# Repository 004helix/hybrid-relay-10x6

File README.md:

# 10-channel hybrid relay din-rail module

- 4 units width
- 12/24v dc input
- reverse polarity protection
- mechanical relay sockets - `Finder 93.11`
- reinforced insulation using `VOT8024AG` optocouplers
- snubberless triacs as SSR - `BTA12-800BW / BTA16-800BW`
- 250VAC/6A slim mechanical relays - `Finder 34.51 / TE V23092 / Hongfa HF41F`
- MCU - `ATmega164PA-MU / ATmega324PA-MU / ATmega644PA-MU`
- triac test button
- open-drain input

[BOM](BOM.md)

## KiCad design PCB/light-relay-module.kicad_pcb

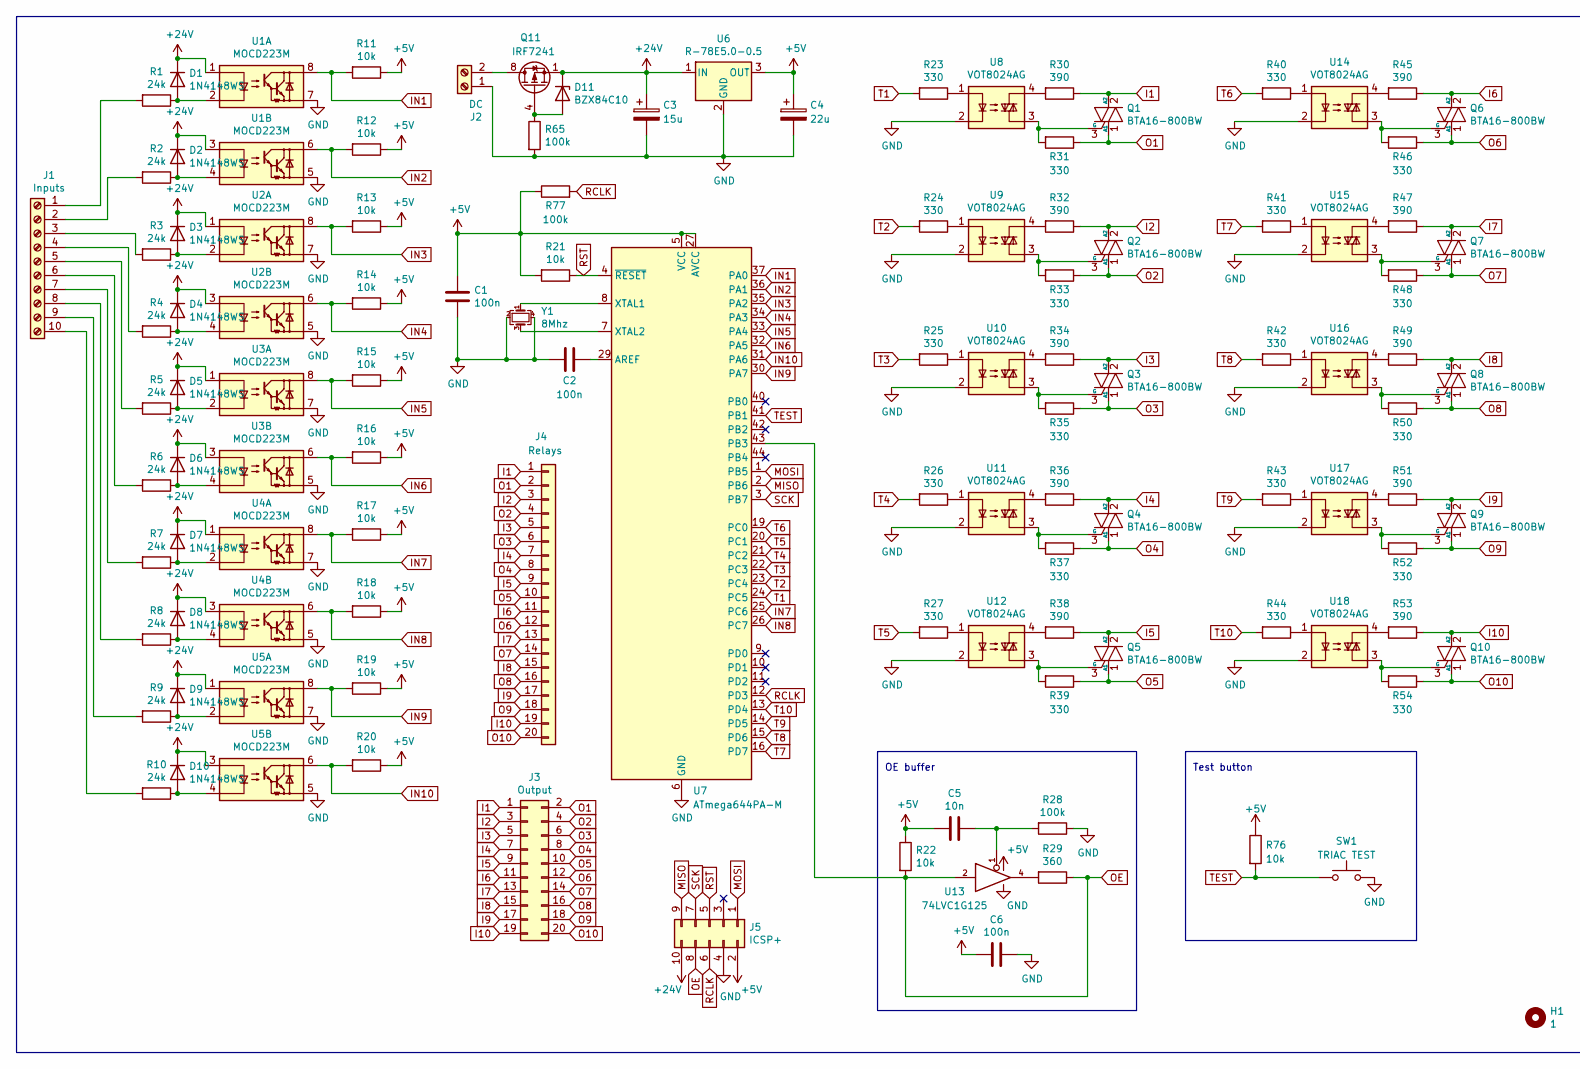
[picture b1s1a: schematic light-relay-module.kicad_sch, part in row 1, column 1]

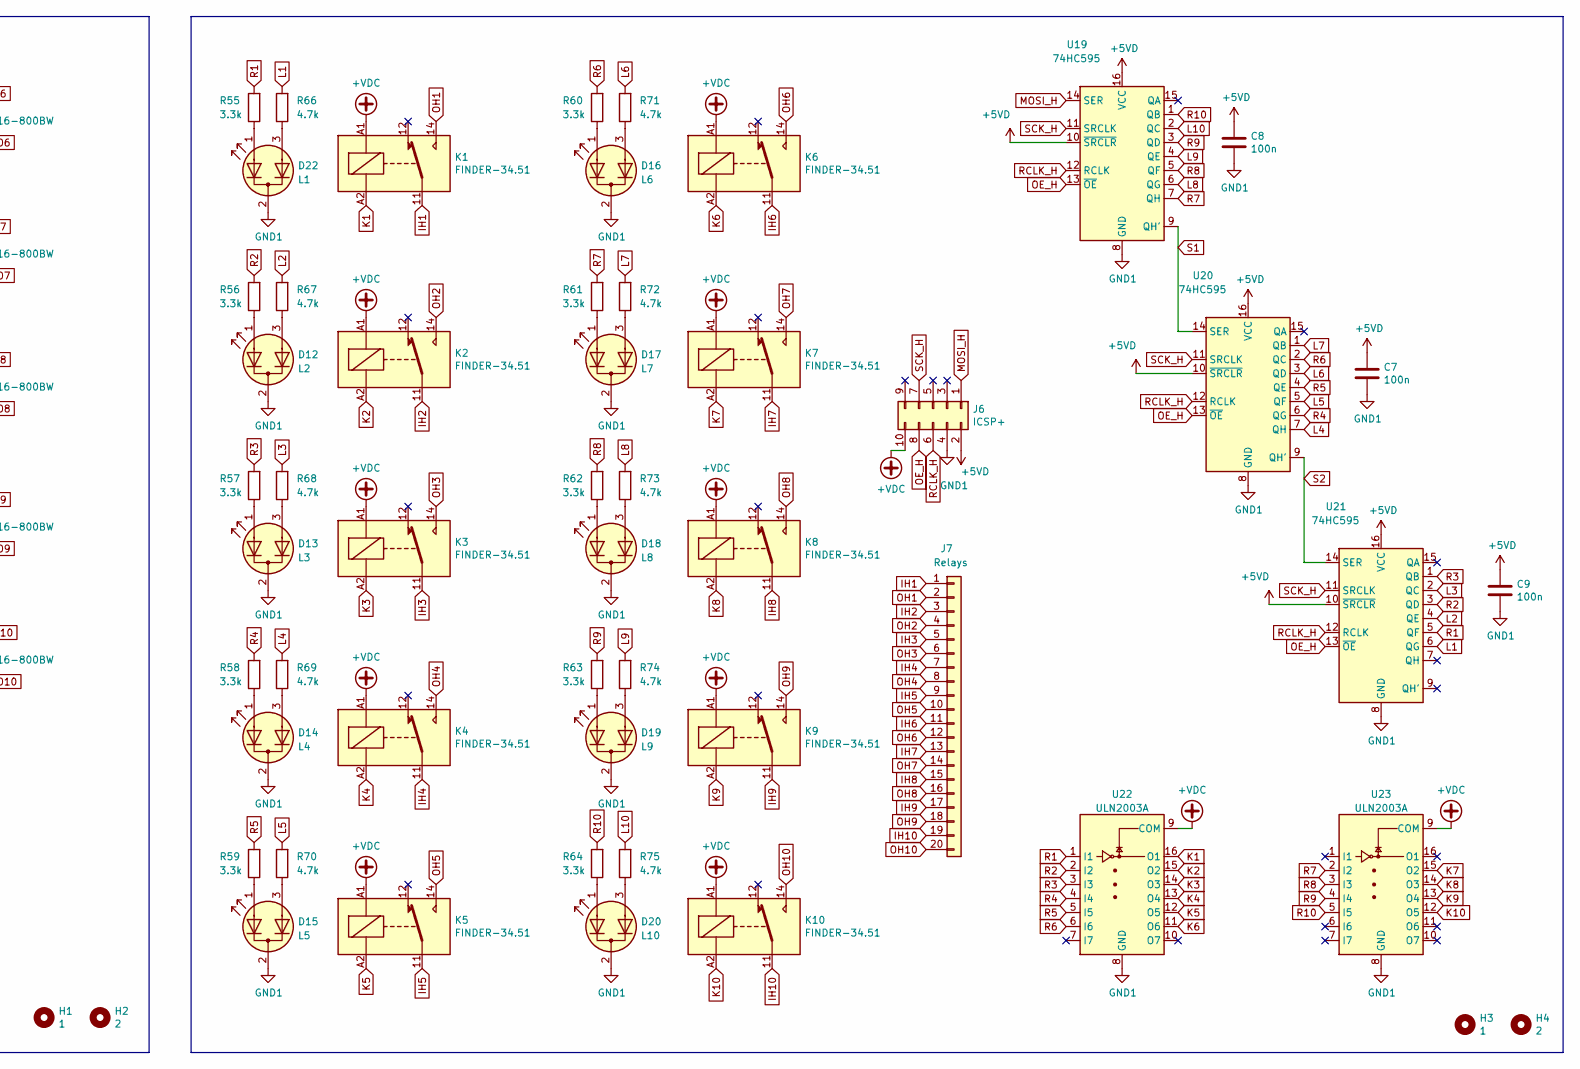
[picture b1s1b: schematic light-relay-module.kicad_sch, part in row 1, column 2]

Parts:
C1, C2, C6, C7, C8, C9: 100n; C_0805_2012Metric
C3: 15u; CP_EIA-7343-40_Kemet-Y
C4: 22u; CP_EIA-3528-21_Kemet-B
C5: 10n; C_0805_2012Metric
D1, D2, D3, D4, D5, D6, D7, D8, D9, D10: 1N4148WS; D_SOD-323
D11: BZX84C10; D_SOT-23_ANK
D12: L2; LED_D3.0mm-3
D13: L3; LED_D3.0mm-3
D14: L4; LED_D3.0mm-3
D15: L5; LED_D3.0mm-3
D16: L6; LED_D3.0mm-3
D17: L7; LED_D3.0mm-3
D18: L8; LED_D3.0mm-3
D19: L9; LED_D3.0mm-3
D20: L10; LED_D3.0mm-3
D22: L1; LED_D3.0mm-3
H1, H3: 1; MountingHole_3.2mm_M3
H2, H4: 2; MountingHole_3.2mm_M3
J1: Inputs; DG141R-10P
J2: DC; TerminalBlock_Phoenix_MKDS-1,5-2_1x02_P5.00mm_Horizontal
J3: Output; DG500B-10P
J4, J7: Relays; Y20P
J5: ICSP+; PinHeader_2x05_P2.54mm_Vertical
J6: ICSP+; PinSocket_2x05_P2.54mm_Vertical
K1, K2, K3, K4, K5, K6, K7, K8, K9, K10: FINDER-34.51; Relay_SPDT_Finder_34.11
Q1, Q2, Q3, Q4, Q5, Q6, Q7, Q8, Q9, Q10: BTA16-800BW; TO-220-3_Vertical
Q11: IRF7241; SOIC-8_3.9x4.9mm_P1.27mm
R1, R2, R3, R4, R5, R6, R7, R8, R9, R10: 24k; R_0603_1608Metric
R11, R12, R13, R14, R15, R16, R17, R18, R19, R20, R21, R22, R76: 10k; R_0603_1608Metric
R23, R24, R25, R26, R27, R40, R41, R42, R43, R44: 330; R_0603_1608Metric
R28, R65, R77: 100k; R_0603_1608Metric
R29: 360; R_0603_1608Metric
R30, R32, R34, R36, R38, R45, R47, R49, R51, R53: 390; R_2512_6332Metric
R31, R33, R35, R37, R39, R46, R48, R50, R52, R54: 330; R_2512_6332Metric
R55, R56, R57, R58, R59, R60, R61, R62, R63, R64: 3.3k; R_0603_1608Metric
R66, R67, R68, R69, R70, R71, R72, R73, R74, R75: 4.7k; R_0603_1608Metric
SW1: TRIAC TEST; SW_Push_1P1T_NO_6x6mm_H9.5mm
U1, U2, U3, U4, U5: MOCD223M; SO-8_3.9x4.9mm_P1.27mm
U6: R-78E5.0-0.5; Converter_DCDC_RECOM_R-78E-0.5_THT
U7: ATmega644PA-M; QFN-44-1EP_7x7mm_P0.5mm_EP5.2x5.2mm
U8, U9, U10, U11, U12, U14, U15, U16, U17, U18: VOT8024AG; DIP-4_W7.62mm
U13: 74LVC1G125; SOT-23-5
U19, U20, U21: 74HC595; TSSOP-16_4.4x5mm_P0.65mm
U22, U23: ULN2003A; TSSOP-16_4.4x5mm_P0.65mm
Y1: 8Mhz; Crystal_SMD_5032-4Pin_5.0x3.2mm

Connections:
+5V: C1.1, C4.1, C5.2, C6.2, J5.2, R11.1, R12.1, R13.1, R14.1, R15.1, R16.1, R17.1, R18.1, R19.1, R20.1, R21.2, R22.1, R76.1, R77.1, U6.3 (OUT), U7.5 (VCC), U7.17 (VCC), U7.27 (AVCC), U7.38 (VCC), U13.5 (VCC)
+5VD: C7.1, C8.1, C9.1, J6.2, U19.10 (~SRCLR), U19.16 (VCC), U20.10 (~SRCLR), U20.16 (VCC), U21.10 (~SRCLR), U21.16 (VCC)
+24V: C3.1, D1.1 (K), D2.1 (K), D3.1 (K), D4.1 (K), D5.1 (K), D6.1 (K), D7.1 (K), D8.1 (K), D9.1 (K), D10.1 (K), D11.1 (K), J5.10, Q11.1 (S), Q11.2 (S), Q11.3 (S), U1.1, U1.3, U2.1, U2.3, U3.1, U3.3, U4.1, U4.3, U5.1, U5.3, U6.1 (IN)
+VDC: J6.10, K1.A1, K2.A1, K3.A1, K4.A1, K5.A1, K6.A1, K7.A1, K8.A1, K9.A1, K10.A1, U22.9 (COM), U23.9 (COM)
GND: C1.2, C2.2, C3.2, C4.2, C6.1, J2.1, J5.4, R28.1, R65.2, SW1.2, U1.5, U1.7, U2.5, U2.7, U3.5, U3.7, U4.5, U4.7, U5.5, U5.7, U6.2 (GND), U7.6 (GND), U7.18 (GND), U7.28 (GND), U7.39 (GND), U7.45 (GND), U8.2, U9.2, U10.2, U11.2, U12.2, U13.3 (GND), U14.2, U15.2, U16.2, U17.2, U18.2, Y1.2, Y1.4
GND1: C7.2, C8.2, C9.2, D12.2 (K), D13.2 (K), D14.2 (K), D15.2 (K), D16.2 (K), D17.2 (K), D18.2 (K), D19.2 (K), D20.2 (K), D22.2 (K), J6.4, U19.8 (GND), U20.8 (GND), U21.8 (GND), U22.8 (GND), U23.8 (GND)
I1: J3.1, J4.1, Q1.2 (A2), R30.1
I2: J3.3, J4.3, Q2.2 (A2), R32.1
I3: J3.5, J4.5, Q3.2 (A2), R34.1
I4: J3.7, J4.7, Q4.2 (A2), R36.1
I5: J3.9, J4.9, Q5.2 (A2), R38.1
I6: J3.11, J4.11, Q6.2 (A2), R45.1
I7: J3.13, J4.13, Q7.2 (A2), R47.1
I8: J3.15, J4.15, Q8.2 (A2), R49.1
I9: J3.17, J4.17, Q9.2 (A2), R51.1
I10: J3.19, J4.19, Q10.2 (A2), R53.1
IH1: J7.1, K1.11
IH2: J7.3, K2.11
IH3: J7.5, K3.11
IH4: J7.7, K4.11
IH5: J7.9, K5.11
IH6: J7.11, K6.11
IH7: J7.13, K7.11
IH8: J7.15, K8.11
IH9: J7.17, K9.11
IH10: J7.19, K10.11
IN1: R11.2, U1.8, U7.37 (PA0)
IN2: R12.2, U1.6, U7.36 (PA1)
IN3: R13.2, U2.8, U7.35 (PA2)
IN4: R14.2, U2.6, U7.34 (PA3)
IN5: R15.2, U3.8, U7.33 (PA4)
IN6: R16.2, U3.6, U7.32 (PA5)
IN7: R17.2, U4.8, U7.25 (PC6)
IN8: R18.2, U4.6, U7.26 (PC7)
IN9: R19.2, U5.8, U7.30 (PA7)
IN10: R20.2, U5.6, U7.31 (PA6)
K1: K1.A2, U22.16 (O1)
K2: K2.A2, U22.15 (O2)
K3: K3.A2, U22.14 (O3)
K4: K4.A2, U22.13 (O4)
K5: K5.A2, U22.12 (O5)
K6: K6.A2, U22.11 (O6)
K7: K7.A2, U23.15 (O2)
K8: K8.A2, U23.14 (O3)
K9: K9.A2, U23.13 (O4)
K10: K10.A2, U23.12 (O5)
L1: R66.2, U21.6 (QG)
L2: R67.2, U21.4 (QE)
L3: R68.2, U21.2 (QC)
L4: R69.2, U20.7 (QH)
L5: R70.2, U20.5 (QF)
L6: R71.2, U20.3 (QD)
L7: R72.2, U20.1 (QB)
L8: R73.2, U19.6 (QG)
L9: R74.2, U19.4 (QE)
L10: R75.2, U19.2 (QC)
MISO: J5.9, U7.2 (PB6)
MOSI: J5.1, U7.1 (PB5)
MOSI_H: J6.1, U19.14 (SER)
unnamed: C2.1, U7.29 (AREF)
unnamed: C5.1, R28.2, U13.1
unnamed: D1.2 (A), R1.1, U1.2
unnamed: D2.2 (A), R2.1, U1.4
unnamed: D3.2 (A), R3.1, U2.2
unnamed: D4.2 (A), R4.1, U2.4
unnamed: D5.2 (A), R5.1, U3.2
unnamed: D6.2 (A), R6.1, U3.4
unnamed: D7.2 (A), R7.1, U4.2
unnamed: D8.2 (A), R8.1, U4.4
unnamed: D9.2 (A), R9.1, U5.2
unnamed: D10.2 (A), R10.1, U5.4
unnamed: D11.2 (A), Q11.4 (G), R65.1
unnamed: D12.1 (A1), R56.1
unnamed: D12.3 (A2), R67.1
unnamed: D13.1 (A1), R57.1
unnamed: D13.3 (A2), R68.1
unnamed: D14.1 (A1), R58.1
unnamed: D14.3 (A2), R69.1
unnamed: D15.1 (A1), R59.1
unnamed: D15.3 (A2), R70.1
unnamed: D16.1 (A1), R60.1
unnamed: D16.3 (A2), R71.1
unnamed: D17.1 (A1), R61.1
unnamed: D17.3 (A2), R72.1
unnamed: D18.1 (A1), R62.1
unnamed: D18.3 (A2), R73.1
unnamed: D19.1 (A1), R63.1
unnamed: D19.3 (A2), R74.1
unnamed: D20.1 (A1), R64.1
unnamed: D20.3 (A2), R75.1
unnamed: D22.1 (A1), R55.1
unnamed: D22.3 (A2), R66.1
unnamed: J1.1, R1.2
unnamed: J1.2, R2.2
unnamed: J1.3, R3.2
unnamed: J1.4, R4.2
unnamed: J1.5, R5.2
unnamed: J1.6, R6.2
unnamed: J1.7, R7.2
unnamed: J1.8, R8.2
unnamed: J1.9, R9.2
unnamed: J1.10, R10.2
unnamed: J2.2, Q11.5 (D), Q11.6 (D), Q11.7 (D), Q11.8 (D)
unnamed: Q1.3 (G), R31.2, U8.3
unnamed: Q2.3 (G), R33.2, U9.3
unnamed: Q3.3 (G), R35.2, U10.3
unnamed: Q4.3 (G), R37.2, U11.3
unnamed: Q5.3 (G), R39.2, U12.3
unnamed: Q6.3 (G), R46.2, U14.3
unnamed: Q7.3 (G), R48.2, U15.3
unnamed: Q8.3 (G), R50.2, U16.3
unnamed: Q9.3 (G), R52.2, U17.3
unnamed: Q10.3 (G), R54.2, U18.3
unnamed: R23.1, U8.1
unnamed: R24.1, U9.1
unnamed: R25.1, U10.1
unnamed: R26.1, U11.1
unnamed: R27.1, U12.1
unnamed: R29.2, U13.4
unnamed: R30.2, U8.4
unnamed: R32.2, U9.4
unnamed: R34.2, U10.4
unnamed: R36.2, U11.4
unnamed: R38.2, U12.4
unnamed: R40.1, U14.1
unnamed: R41.1, U15.1
unnamed: R42.1, U16.1
unnamed: R43.1, U17.1
unnamed: R44.1, U18.1
unnamed: R45.2, U14.4
unnamed: R47.2, U15.4
unnamed: R49.2, U16.4
unnamed: R51.2, U17.4
unnamed: R53.2, U18.4
unnamed: U7.7 (XTAL2), Y1.3
unnamed: U7.8 (XTAL1), Y1.1
O1: J3.2, J4.2, Q1.1 (A1), R31.1
O2: J3.4, J4.4, Q2.1 (A1), R33.1
O3: J3.6, J4.6, Q3.1 (A1), R35.1
O4: J3.8, J4.8, Q4.1 (A1), R37.1
O5: J3.10, J4.10, Q5.1 (A1), R39.1
O6: J3.12, J4.12, Q6.1 (A1), R46.1
O7: J3.14, J4.14, Q7.1 (A1), R48.1
O8: J3.16, J4.16, Q8.1 (A1), R50.1
O9: J3.18, J4.18, Q9.1 (A1), R52.1
O10: J3.20, J4.20, Q10.1 (A1), R54.1
OE: J5.8, R22.2, R29.1, U7.43 (PB3), U13.2
OE_H: J6.8, U19.13 (~OE), U20.13 (~OE), U21.13 (~OE)
OH1: J7.2, K1.14
OH2: J7.4, K2.14
OH3: J7.6, K3.14
OH4: J7.8, K4.14
OH5: J7.10, K5.14
OH6: J7.12, K6.14
OH7: J7.14, K7.14
OH8: J7.16, K8.14
OH9: J7.18, K9.14
OH10: J7.20, K10.14
R1: R55.2, U21.5 (QF), U22.1 (I1)
R2: R56.2, U21.3 (QD), U22.2 (I2)
R3: R57.2, U21.1 (QB), U22.3 (I3)
R4: R58.2, U20.6 (QG), U22.4 (I4)
R5: R59.2, U20.4 (QE), U22.5 (I5)
R6: R60.2, U20.2 (QC), U22.6 (I6)
R7: R61.2, U19.7 (QH), U23.2 (I2)
R8: R62.2, U19.5 (QF), U23.3 (I3)
R9: R63.2, U19.3 (QD), U23.4 (I4)
R10: R64.2, U19.1 (QB), U23.5 (I5)
RCLK: J5.6, R77.2, U7.12 (PD3)
RCLK_H: J6.6, U19.12 (RCLK), U20.12 (RCLK), U21.12 (RCLK)
RST: J5.5, R21.1, U7.4 (~RESET)
S1: U19.9 (QH'), U20.14 (SER)
S2: U20.9 (QH'), U21.14 (SER)
SCK: J5.7, U7.3 (PB7)
SCK_H: J6.7, U19.11 (SRCLK), U20.11 (SRCLK), U21.11 (SRCLK)
T1: R23.2, U7.24 (PC5)
T2: R24.2, U7.23 (PC4)
T3: R25.2, U7.22 (PC3)
T4: R26.2, U7.21 (PC2)
T5: R27.2, U7.20 (PC1)
T6: R40.2, U7.19 (PC0)
T7: R41.2, U7.16 (PD7)
T8: R42.2, U7.15 (PD6)
T9: R43.2, U7.14 (PD5)
T10: R44.2, U7.13 (PD4)
TEST: R76.2, SW1.1, U7.41 (PB1)

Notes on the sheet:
OE buffer
Test button

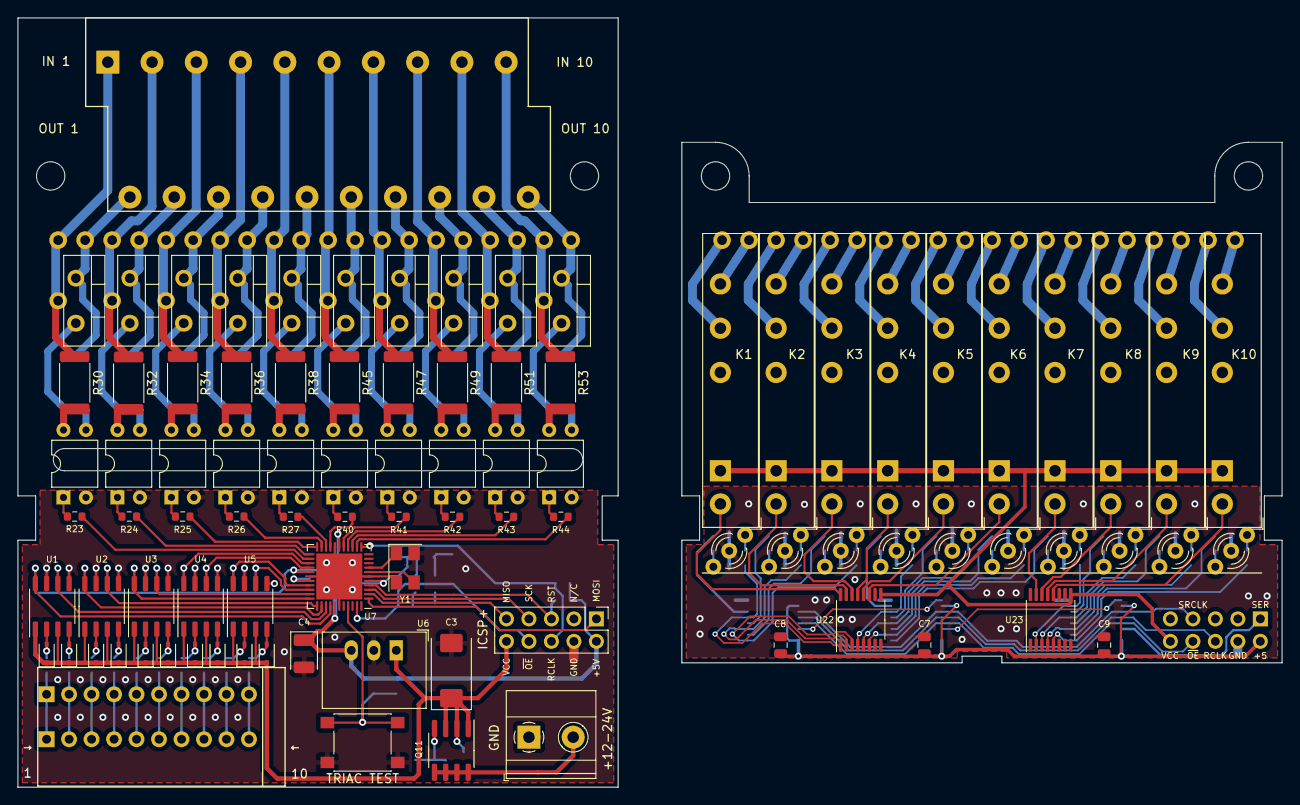
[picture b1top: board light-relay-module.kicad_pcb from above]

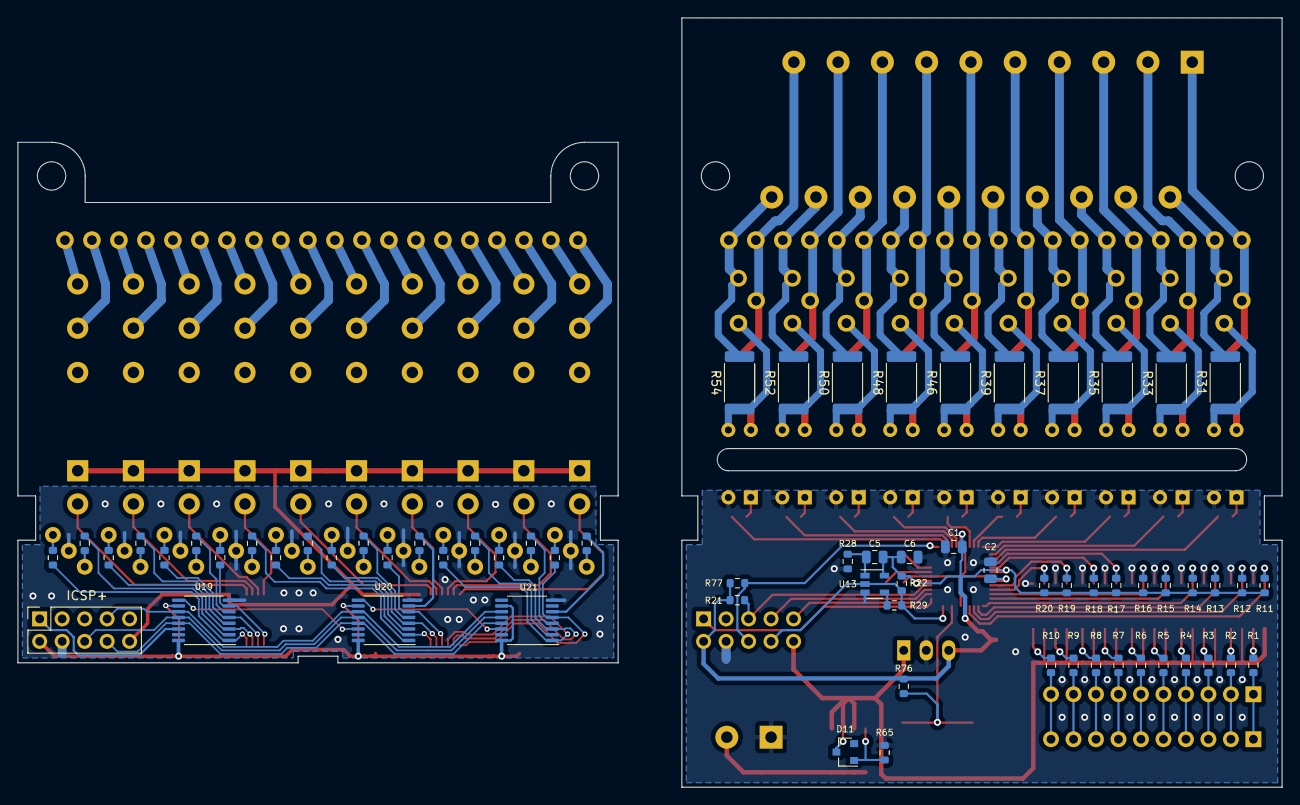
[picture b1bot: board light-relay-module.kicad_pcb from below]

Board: 2 copper layers, 142.8 x 86.9 mm, 164 parts (67 on the bottom side), 186 nets.

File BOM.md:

# BOM

| Ref Des                                 | Qty | Manufacturer             | Mfg Part #                                | Description / Value            | Package       |
| --------------------------------------- | --- | ------------------------ | ----------------------------------------- | ------------------------------ | ------------- |
| U1-U5                                   | 5   | onsemi                   | MOCD223M                                  | Darlington Output Optocouplers | SOIC-8        |
| U6                                      | 1   | Mornsun / Recon / Aimtec | K7805-500R3 / R-78E5.0-0.5 / AMSR-7805-NZ | DC-DC converter                | SIP-3         |
| U7                                      | 1   | Microchip Technology     | ATmega164PA/324PA/644PA-MU                | MCU                            | VQFN-44       |
| U8-U12,U14-U18                          | 10  | Vishay Semiconductors    | VOT8024AG                                 | Opto-triac                     | DIP-4         |
| U13                                     | 1   | Texas Instruments        | SN74LVC1G125DBVR                          | Single Bus Buffer Gate         | SOT-23-5      |
| U19-U21                                 | 3   | Nexperia                 | 74HC595PW                                 | 8-bit shift register           | TSSOP-16      |
| U22-U23                                 | 2   | Texas Instruments        | ULN2003APW                                | Darlington transistor array    | TSSOP-16      |
| Y1                                      | 1   | any                      | Crystal 8.000Mhz                          | 8Mhz                           | SMD 5032 4Pin |
| SW1                                     | 1   | any                      | Push button                               |                                | SMD 6*6mm     |
| C1-C2,C6-C9                             | 7   | any                      | 100nF                                     | Capacitor                      | 0805          |
| C3                                      | 1   | any                      | 15/22uF 35v                               | Tantalum Capacitor             | SMD D         |
| C4                                      | 1   | any                      | 15/22uF 10v                               | Tantalum Capacitor             | SMD A         |
| C5                                      | 1   | any                      | 10nF                                      | Capacitor                      | 0805          |
| D1-D10                                  | 10  | any                      | 1N4148WS                                  | Diode                          | SOD-323       |
| D11                                     | 1   | any                      | BZX84C10                                  | Zener diode 10V                | SOT-23        |
| D12-D22                                 | 10  | G-NOR                    | GNL-3015UEUGW                             | Red/Green 3mm LED              | THT           |
| J1                                      | 1   | Degson / Phoenix Contact | DG141R-2.54-10P / 1789333                 |                                | THT           |
| J2                                      | 1   | any                      | Terminal block 5mm 2Pin                   |                                | THT           |
| J3                                      | 5   | Degson / KLS Electronic  | DG500B-5.0-04P / KLS2-128IB-5.00-04P      |                                | THT           |
| J4,J7                                   | 20  | any                      | 35mm winding wire D0.8-1.0mm              |                                | THT           |
| J5                                      | 1   | any                      | 2.54mm 2x5 Pin Header                     |                                | THT           |
| J6                                      | 1   | any                      | 2.54mm 2x5 Pin Socket                     |                                | THT           |
| -                                       | 1   | any                      | 2.54mm 2x5 Pin Socket Long Needle         |                                | THT           |
| K1-K10                                  | 10  | Finder                   | Finder 93.11                              | Relay Socket                   | THT           |
| -                                       | 10  | Finder / Hongfa          | 34.51.7 / HF41F                           | Relay 12/24v                   | THT           |
| Q1-Q10                                  | 10  | STMicroelectronics       | BTA12-800BWRG / BTA16-800BWRG             | Snubberless triac              | THT           |
| Q11                                     | 1   | Infineon Technologies    | IRF7241                                   | P-Channel MOSFET               | SO-8          |
| R1-R10                                  | 10  | any                      | 24k                                       | Resistor                       | 0603          |
| R11-R22,R76                             | 13  | any                      | 10k                                       | Resistor                       | 0603          |
| R23-R27,R40-R44                         | 10  | any                      | 330                                       | Resistor                       | 0603          |
| R28,R65,R77                             | 3   | any                      | 100k                                      | Resistor                       | 0603          |
| R29                                     | 1   | any                      | 360                                       | Resistor                       | 0603          |
| R30,R32,R34,R36,R38,R45,R47,R49,R51,R53 | 10  | any                      | 390                                       | Resistor                       | 2512          |
| R31,R33,R35,R37,R39,R46,R48,R50,R52,R54 | 10  | any                      | 330                                       | Resistor                       | 2512          |
| R55-R64                                 | 10  | any                      | 3.3k                                      | Resistor                       | 0603          |
| R66-R75                                 | 10  | any                      | 4.7k                                      | Resistor                       | 0603          |
| -                                       | 1   | Gainta                   | D4MG                                      | Chassis                        |               |

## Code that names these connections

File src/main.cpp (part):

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#define MHZ 1000000ULL

// shift register array and button pins
#define RCLK        PIN_PD3
#define OE          PIN_PB3
#define SER_IN      PIN_SPI_MOSI  // PB5
#define SRCK        PIN_SPI_SCK   // PB7
#define TRIAC_TEST  PIN_PB1

// spi settings
SPISettings ss(4*MHZ, MSBFIRST, SPI_MODE0);
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
// triacs (pins) and triac leds (shift registers)
uint8_t triac[10] = {
    PIN_PC5, PIN_PC4, PIN_PC3, PIN_PC2, PIN_PC1,
    PIN_PC0, PIN_PD7, PIN_PD6, PIN_PD5, PIN_PD4
};
struct {
    uint8_t uc;
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    }

    cli();
    // disable PA0-PA7 pull-ups
    PORTA = 0;
    // PA0-PA7 inputs
    DDRA = 0;
    // disable PB0-PB3,PB5-PB7 pull-ups, PB4 (SS) to low
    PORTB = 0;
    // PB4 (SS) output
    DDRB = (1 << DDB4);
    // disable PC6-PC7 pull-ups, PC0-PC5 to low
    PORTC = 0;
    // PC0-PC5 outputs
    DDRC = (1 << DDC5) | (1 << DDC4) | (1 << DDC3) | (1 << DDC2) | (1 << DDC1) | (1 << DDC0);
    // disable PD0-PD2 pull-ups, PD3 (RCLK) to high, PD4-PD7 to low
    PORTD = (1 << PD3);
    // PD3-PD7 outputs
    DDRD = (1 << DDD7) | (1 << DDD6) | (1 << DDD5) | (1 << DDD4) | (1 << DDD3);
    // PCINT0-PCINT7
    PCMSK0 = (1 << PCINT7) | (1 << PCINT6) | (1 << PCINT5) | (1 << PCINT4) | (1 << PCINT3) | (1 << PCINT2) | (1 << PCINT1) | (1 << PCINT0);
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
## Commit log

2022-05-25 fix CH_OFF2ON_2 if test button pressed
2022-05-25 Add BOM, rename optocouplers

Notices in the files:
src/main.cpp:
This file is released under the GPL.
